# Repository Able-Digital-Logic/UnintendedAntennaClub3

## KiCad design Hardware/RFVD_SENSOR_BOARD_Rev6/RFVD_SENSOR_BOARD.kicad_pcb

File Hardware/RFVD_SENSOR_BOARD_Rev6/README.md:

# RFVD SENSOR-D board: layout handoff (2026-10-02)

This folder holds a complete KiCad 10 project of the RFVD sensor board. Placement is final and locked, and 92.6% of the board is routed (42 links left, each with a mapped path). You can open it and keep routing.

**To finish the routing, start with [`docs/ROUTING_FINISH_GUIDE.md`](docs/ROUTING_FINISH_GUIDE.md).**

**2026-10-07: ECO-002 and ECO-003 landed.** Records: `03_hardware/ECO-002_POWER_MODES.md` and `03_hardware/ECO-003_HIERARCHY_AND_LABELING.md` in the main repo.
- **ECO-002, two battery modes:**
  - SCREEN: a TPS62913 buck locked to 3 × fs;
  - RECORD: a TPS7A4701 LDO with the buck off;
  - an NFM18 RF filter (FL1301) on +3V3_A.
- **ECO-003, schematic reorganised:**
  - hierarchical sheets with a block-diagram root page, sheet index, bus-alias table and legend;
  - rail power symbols;
  - every sheet's bus ports grouped in a "SHEET INTERFACE" block;
  - designators renumbered by page (page × 100 + index, e.g. R1301), with old-to-new in [`docs/REFERENCE_MAP_ECO-003.md`](docs/REFERENCE_MAP_ECO-003.md);
  - Values carry ratings.
- **Rules:** DRU v13 and the net classes follow the renamed nets.
- **PCB:** the new parts are placed with the EMC rules, and the stale copper of the old buck and +3V3_A node is removed. DRC shows 0 shorts. Routing to do for the ECO area: [`docs/LAYOUT_STATUS.md`](docs/LAYOUT_STATUS.md), top section.
- **Placement pass (late 2026-10-07):** the TPS62913 buck (U1301) is re-laid to TI's recommended layout (SLVSFP4B Fig. 10-1): 0.7 mm switch node, input caps on the VIN/PGND pins, output-cap ground beside PGND. The LDO output cap C1311, FL1301, R1211 and TP1104 moved closer to their partners. No new copper DRC errors; the ratsnest is 27 mm shorter. Pin positions and escape vias for the hand router: `docs/LAYOUT_STATUS.md`, top section.

**Checkpoint 5 (2026-10-04), board sha256 `f9fb559366`: final state of this pass, ready for hand routing.**
- **DRC: 0 errors**, 110 warnings, sign-off PASS.
- **42 open links, 0 blocked.** `docs/ROUTING_FINISH_GUIDE.md` §0 lists each link with a suggested path and its hand-off via.
- Placement is final and every footprint is locked.
- Ratsnest 3522 mm (m17: 4018). BOM: 100 lines / 309 parts.
- Since checkpoint 4a:
  - J10 moved 0.96 mm to match the HRO drawing;
  - F1 on its Bourns Style 2 land at J2, with PACK+ as a 1 mm B-only run;
  - the U403 buffer moved out from under J10;
  - the BOM consolidation (firmware rules in FIRMWARE_CONTRACT §11);
  - the remaining DRC fixes;
  - pad escapes for every blocked link.

**Checkpoint 4a (2026-10-04), board sha256 `08570ddf0b`.**
- Five region hand-layout packages: A RF/AFE, B1/B2 MCU core, C power band, E south J11/J2. The sourcing package moved 47 parts to in-stock JLC Basic or FOJAN types and C31 to 25 V.
- **DRC 278 → 109 errors**, 116 warnings, 43 open links (was 44), missing return vias 45 → 13, neck chains 46 → 12. Sign-off PASS. ERC 0.
- What was added:
  - an AFE GND ring: a 1.0 mm band under a mask-open strip, 19 fence vias, FL1 on the east wall;
  - the 32 kHz crystal-gap via moved out of the gap;
  - the EXP_SYNC fix at J11;
  - the VSYS island at U402 routed;
  - battery trunks at 0.8 mm on In3;
  - BQ25798 hot-loop GND vias;
  - 31 edge-stitching vias.
- Next: the routing waves for the remaining errors and links (west/J10, MCU-core seam, battery, then the LCD and expansion buses).

**Checkpoint 3 (2026-10-04), board sha256 `527e801c62`.**
- The stricter rules v11 landed: side-aware exemptions, neck caps, In3 power widths, missing keep-outs, pre-defined sizes, mask 0.
- Every stale sheet note and Function field was corrected.
- DRC now shows **278 errors**, on purpose. They are the copper the old rules hid (power widths and necks, 3W spacing, foreign copper under J10), and they are checkpoint 4's routing work list (`docs/LAYOUT_STATUS.md`, Checkpoint 3).
- ERC 0, 44 open links, sign-off rules PASS.

**Checkpoint 2b (2026-10-04), board sha256 `f539f0317c`. DRC: 0 errors.**
- **SD:** an ST EMIF06 SD front end replaces 20 parts and clears both SD skew errors.
- **PSRAM:** one series array.
- **Display bus:** resistors regrouped by pin side.
- **MCU/service:** SWO, the BOOT button and the lid interrupt are removed; the buttons get series resistors.
- **Expansion:** pull-ups added, ESD flow-through, the MR-kill jumpers are gone.
- **Back silkscreen:** an issue date and a serial-number box. A fab note sits on User.Drawings.
- **J10:** pin-in-paste on its shell.

Totals: 538/582 routed (44 open), 82 warnings (each explained in `docs/LAYOUT_STATUS.md`), sign-off PASS. JLC BOM: 106 lines / 318 parts. The manufacturing spec and the panel tool are in `docs/MANUFACTURING_EMC_SPEC.md` and `tools/make_panel.py`; the panel is a 72 × 90 mm 1-up frame, so exactly 2 boards are assembled.

**Checkpoint 2a (2026-10-04), board sha256 `c4383fe7ab`.** The circuit changes from the critique landed:
- the AD7380 runs on its internal reference;
- the EREF filter is a single pole;
- 33R / 2.2 nF ADC reservoirs;
- buck FB divider 23.2k/10k;
- eFuse OVLO 64.9k;
- display straps in copper and a write-only bus;
- the VSYS and VBUS dividers, the charge LED and two polymer caps are gone;
- the 1 µF line merged.

30 parts removed, 2 added. DRC: 2 errors (both `skew_sdmmc`, until SD_D1 is routed), 85 warnings; sign-off PASS. ERC is clean. 47 open links (was 50). The JLC BOM is 105 lines / 346 parts (was 111 / 369). An independent review checked every change against its datasheet. Details: `docs/LAYOUT_STATUS.md` (Checkpoint 2a); firmware consequences: `docs/FIRMWARE_NOTES.md`.

**Checkpoint 1 (2026-10-04), board sha256 `5c22d06d54`.** The first batch from the full design critique and the placement revision landed:
- placement and EMC fixes in the RF, analog, expansion, charger/USB, buck and battery areas;
- a 22.9 mm antenna stub deleted;
- overlapping drills fixed;
- silkscreen labels and the board ID moved onto the board;
- schematic DNP flags fixed, so the BOM now includes the FB1 damper.

DRC warnings went from 97 to 87 (counted in this folder), ERC is clean, and no connection got worse. Details: `docs/LAYOUT_STATUS.md` (Checkpoint 1); the plan for the rest: `docs/WORKPLAN_2026-10-03.md`.

**Update 2026-10-03 (hand-layout pass, no auto-routers):**
- Every edit was an explicit coordinate list (`docs/hand_edits_2026-10-03/`).
- **DRC errors 14 → 3; warnings 212 → 153.** The VSYS trunk is closed.
- R304, R411, R404 and R417 were re-placed. The BUCK_SYNC spacing now passes the 3W and the 3 mm LSE sign-off rules.
- The rest of the board is handed over for interactive push-and-shove routing, with a measured, step-by-step guide.
- J3 has no legal alternative pose (checked), so the band is solved by re-fanning escapes, not by moving the big parts.

**Update 2026-10-02 night:**
- The board was **widened to 52.05 x 90.05 mm**: +2.5 mm per side, with a notch that keeps the USB-C and microSD flush.
- A connection-length **placement audit** was added: `docs/PLACEMENT_AUDIT.md` and `outputs/RFVD_placement_audit_*`.
- R314 and Q302 moved next to their partners, and 5 more connections plus all GND islands were routed.
- A DRC clean-up took the errors from 50 to 14:
  - shield pads now connect solidly to the GND pours;
  - an SWDIO via too close to a J10 hole was re-routed, and the router now models that rule;
  - 3 clearance problems were re-routed locally;
  - two scoped rule exceptions were added (DRU patch v10).
- The tools were cleaned into one self-tested folder: `tools/README.md`.
- The board before this pass is in `backups/RFVD_SENSOR_BOARD_before_widening_2026-10-02.kicad_pcb`.

The project folder `03_hardware/RFVD_SENSOR_BOARD_GITHUB` was **not** modified. Everything here was built from it on scratch copies; the base board hash was `2ccd301640`.

Open **`RFVD_SENSOR_BOARD.kicad_pro`** in KiCad 10. The libraries and 3D models are included and use project-relative paths.

## Status at a glance (checkpoint 5, board sha256 `f9fb559366`)

| Item | State |
|---|---|
| Outline | **52.05 x 90.05 mm** (widened 2026-10-02 from 47.05 mm; port notch at y 104.6-133.3 keeps J3/J10 flush). Fits the 56 mm box: west gap 2.75 mm (5.25 at the ports), east 1.25 mm. |
| Placement | **Final and locked**: 341 footprints (196 top / 145 bottom), all locked. Placed against each IC's datasheet layout guide (`docs/sensitivity.json`, with section and page). The 2026-10-04 sign-off on the board: **placeaudit 0 MOVE / 0 OVER**; `tools/dsgap.py` measured 269 datasheet budgets, 264 within budget and 5 justified with measured reasons (`docs/PLACEMENT_DATASHEET_CHECK.md`, `tools/placeaudit_keep.json`). |
| Routing | **524 of 566 connections (92.6%)**; the total was 633 before the BOM consolidation removed parts. **42 open links, 0 blocked**: 12 direct, 30 with a mapped legal path. Every link is in `docs/ROUTING_FINISH_GUIDE.md` §0 with exact coordinates. No GND islands. |
| Copper | 3,038 mm of track (F 994 / In3 1,047 / B 997 mm), 1,028 vias (941 of them 0.45/0.20 POFV), 7 copper zones, 45 rule areas. |
| DRC (`outputs/RFVD_DRC_report.*`) | **0 errors**, 110 warnings (each class explained in `docs/LAYOUT_STATUS.md`, Checkpoint 5; 42 of them are the deliberate hand-off vias), sign-off PASS. Always run DRC with `--all-track-errors` from the CLI. |
| Silkscreen | No reference designator is visible on F/B silkscreen; they stay on the fab layers. |
| BOM | Regenerated by `tools/make_outputs.py` from KiCad's own DNP flags: **100 lines / 309 placed parts**, every one with MPN and LCSC number. The CPL has exactly those designators, rotation-corrected for JLC. Live stock check 2026-10-04 (`docs/LAYOUT_STATUS.md`): 95 lines are in JLC stock for 2 boards and 4 come from LCSC via a parts pre-order. **L1 (XGL4020-472MEC) needs the Global Sourcing route: JLC holds 1.** |
| Fab outputs | **Not generated on purpose** until the last 42 links are routed. Then run `tools/make_fab_outputs.py` and `tools/make_panel.py` (D27: 1-up 72 x 90 mm frame). |

## What is left to route (`outputs/RFVD_unrouted.csv`, `outputs/RFVD_unrouted.png`)

| Group | Open | Nets |
|---|---|---|
| Expansion to J11 | 15 | EXP_3V3_SNS, EXP_ANA_MON, EXP_CS0_N_MCU, EXP_CS1_N_MCU, EXP_DETECT_N_MCU, EXP_GATE, EXP_INT1_N_MCU, EXP_IO0_MCU, EXP_IO1_MCU, EXP_MISO_MCU, EXP_RST_N_MCU, EXP_SPI_MOSI, EXP_SPI_SCK, EXP_SYNC, EXP_VHP_SNS |
| LCD bus to J4 | 14 | LCD_BL, LCD_BL_SW, LCD_CS_N, LCD_D0-LCD_D7, LCD_DC, LCD_LED_K4, LCD_WR_N |
| Power / charger | 6 | CHG_INT_N, QON_N, USB_DM, USB_DP (2 islands), VBAT_RTC |
| Other | 7 | MARK_N, NRST, PSRAM_IO2_RAM, RECORD_N, SD_D1_MCU, TP_INT, TP_SCL |
| GND | 0 | All GND islands are joined. |

Each link, with both ends, the suggested path and its hand-off via, is in **`docs/ROUTING_FINISH_GUIDE.md` §0**. The history and root causes are in `docs/LAYOUT_STATUS.md`.

## What to do next

1. **Do the GUI-only setup steps** in `docs/LEAD_GUI_STEPS.md` (stackup loss, via filling, silk minimums, J10 shell paste). The two optional placement clean-ups (A, B) are listed there too.
2. **Route the 42 open links** with KiCad's interactive router in push-and-shove mode, following `docs/ROUTING_FINISH_GUIDE.md` §0:
   - set the pre-defined sizes first (0.45/0.20 vias, 0.15 mm tracks);
   - start each link from its hand-off via;
   - octilinear tracks, fillets on clocks and strobes.
   Footprints are locked, so push-and-shove moves only tracks.
3. **Add a GND return via** at every layer change of a fast net (R17: within 1.0 mm for clocks, 1.5 mm for digital).
4. **Re-run DRC** with the project rule file (`RFVD_SENSOR_BOARD.kicad_dru`) and `--all-track-errors`; the goal is 0 errors and no new warning class.
5. **Regenerate the outputs**: `tools/make_outputs.py` (run it in this folder), then the fab outputs and the panel (`tools/make_fab_outputs.py`, `tools/make_panel.py --cols 1 --min-size 72`). Check the CPL rotations in JLCPCB's preview before ordering.
6. **Copy the result back** into `RFVD_SENSOR_BOARD_GITHUB`: replace the board, rule file and project file there, or follow the Konnect transfer plan in `docs/CHANGES_FROM_PROJECT.md`.

## Folder map

| Path | Contents |
|---|---|
| `RFVD_SENSOR_BOARD.kicad_pro/.kicad_pcb/.kicad_dru` | Project, routed board (this handoff) and design rules. |
| `*.kicad_sch` | Schematic: root plus 11 sheets, unchanged from the project. |
| `libraries/`, `models/`, `fp-lib-table`, `sym-lib-table` | Custom symbols, footprints and 3D models (project-relative). |
| `outputs/` | BOMs, JLCPCB BOM/CPL, position file, schematic PDF, multi-page layer PDF, DRC report, unrouted list and map. See `outputs/README.md`. |
| `renders/` | 3D renders (top/bottom) and one image per copper layer with footprint outlines (`layer_1_F_Cu.png` ... `layer_6_B_Cu.png`). |
| `docs/` | Board overview, layout status, changes from the project, tools guide, placement sensitivity study, and the original reports (`docs/reference/`). |
| `tools/` | The single, self-tested layout toolset: router, placement audit, placement, widening, merge, DRC and output helpers. Index: `tools/README.md`; check it with `tools/selftest.py`; regenerate every output with `tools/make_outputs.py`. |

## Documents

- `docs/BOARD_OVERVIEW.md`: what the board does, blocks and key parts, stack-up, net classes, EMC strategy, placement philosophy.
- `docs/ROUTING_FINISH_GUIDE.md`: **how to finish the last 50 links interactively**. It covers every link with today's feasibility, the verified unlock moves, the J4 via sites, the rule areas the router does not enforce, router set-up and order of work. Maps are in `docs/routing_guide/`.
- `docs/LAYOUT_STATUS.md`: routing status per group, root causes, recommended fixes, the DRC error list, and decisions and deviations.
- `docs/CHANGES_FROM_PROJECT.md`: everything that differs from `RFVD_SENSOR_BOARD_GITHUB`, and how to bring it back.
- `docs/PLACEMENT_DATASHEET_CHECK.md`: every part against its IC's datasheet layout rule, measured on the board (generated by `tools/dsgap.py`), with the reason for each part kept over its budget.
- `docs/LEAD_GUI_STEPS.md`: the steps only the KiCad GUI can do, and the optional placement clean-ups.
- `docs/PLACEMENT_AUDIT.md`: the placement audit (what was flagged, moved and kept, with reasons) and the board widening.
- `tools/README.md`: the layout tools and how to re-run them (`docs/TOOLS.md` points there).
- `docs/sensitivity_summary.md` / `docs/sensitivity.json`: per-part datasheet placement budgets.
- `docs/reference/`: the project's device report, PCB layout rationale and EMC report (.docx), plus sheet images.

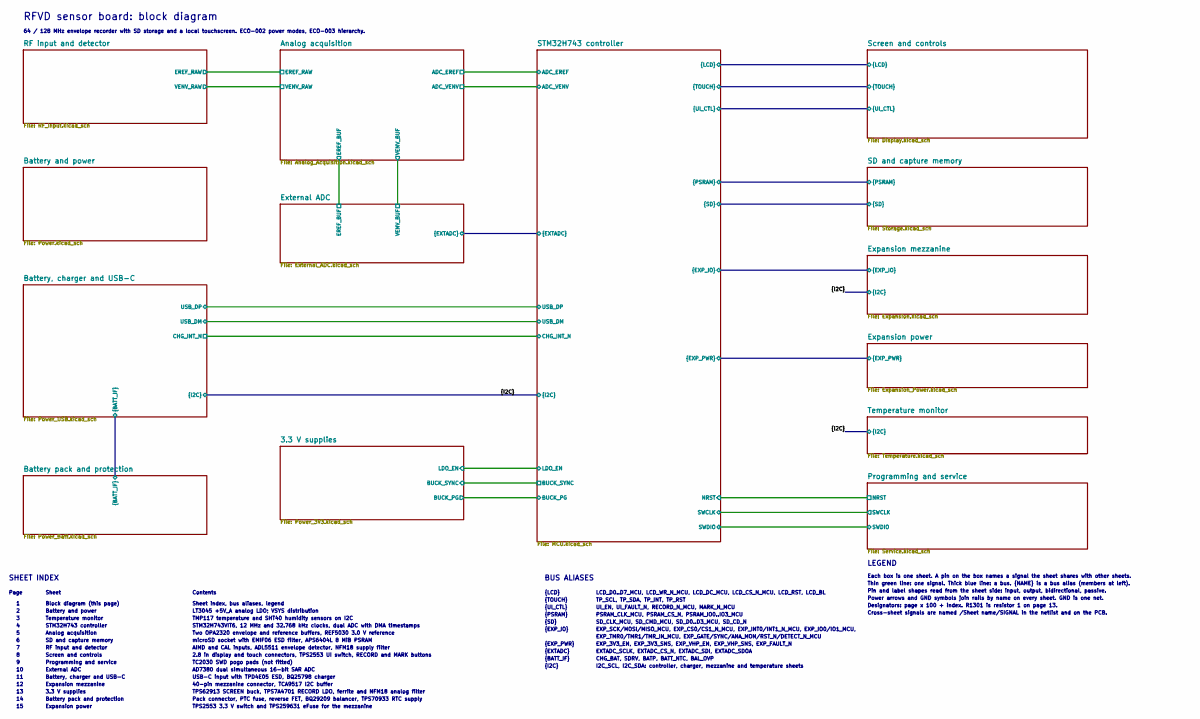
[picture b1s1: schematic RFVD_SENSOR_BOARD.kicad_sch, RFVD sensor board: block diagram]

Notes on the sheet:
TMP117 temperature and SHT40 humidity sensors on I2C
Thin green line: one signal. Thick blue line: a bus. {NAME} is a bus alias (members at left).
Designators: page x 100 + index. R1301 is resistor 1 on page 13.
Sheet index, bus aliases, legend
STM32H743 controller
Programming and service
Pin and label shapes read from the sheet side: input, output, bidirectional, passive.
Power arrows and GND symbols join rails by name on every sheet. GND is one net.
{I2C}
Each box is one sheet. A pin on the box names a signal the sheet shares with other sheets.
Sheet
USB-C input with TPD4E05 ESD, BQ25798 charger
Analog acquisition
LEGEND
TPS62913 SCREEN buck, TPS7A4701 RECORD LDO, ferrite and NFM18 analog filter
SD_CLK_MCU, SD_CMD_MCU, SD_D0..D3_MCU, SD_CD_N
EXP_TMR0/TMR1/TMR_IN_MCU, EXP_GATE/SYNC/ANA_MON/RST_N/DETECT_N_MCU
Pack connector, PTC fuse, reverse FET, BQ29209 balancer, TPS70933 RTC supply
LT3045 +5V_A analog LDO; VSYS distribution
{BATT_IF}
PSRAM_CLK_MCU, PSRAM_CS_N, PSRAM_IO0..IO3_MCU
EXP_SCK/MOSI/MISO_MCU, EXP_CS0/CS1_N_MCU, EXP_INT0/INT1_N_MCU, EXP_IO0/IO1_MCU,
I2C_SCL, I2C_SDA: controller, charger, mezzanine and temperature sheets
Battery and power
Cross-sheet signals are named /Sheet name/SIGNAL in the netlist and on the PCB.
STM32H743VIT6, 12 MHz and 32.768 kHz clocks, dual ADC with DMA timestamps
{EXP_PWR}
Page
{EXP_IO}
Temperature monitor
Battery, charger and USB-C
Contents
AD7380 dual simultaneous 16-bit SAR ADC
{UI_CTL}
CHG_BAT, SDRV, BATP, BATT_NTC, BAL_OVP
UI_EN, UI_FAULT_N, RECORD_N_MCU, MARK_N_MCU
BUS ALIASES
{PSRAM}
RF input and detector
Two OPA2320 envelope and reference buffers, REF5030 3.0 V reference

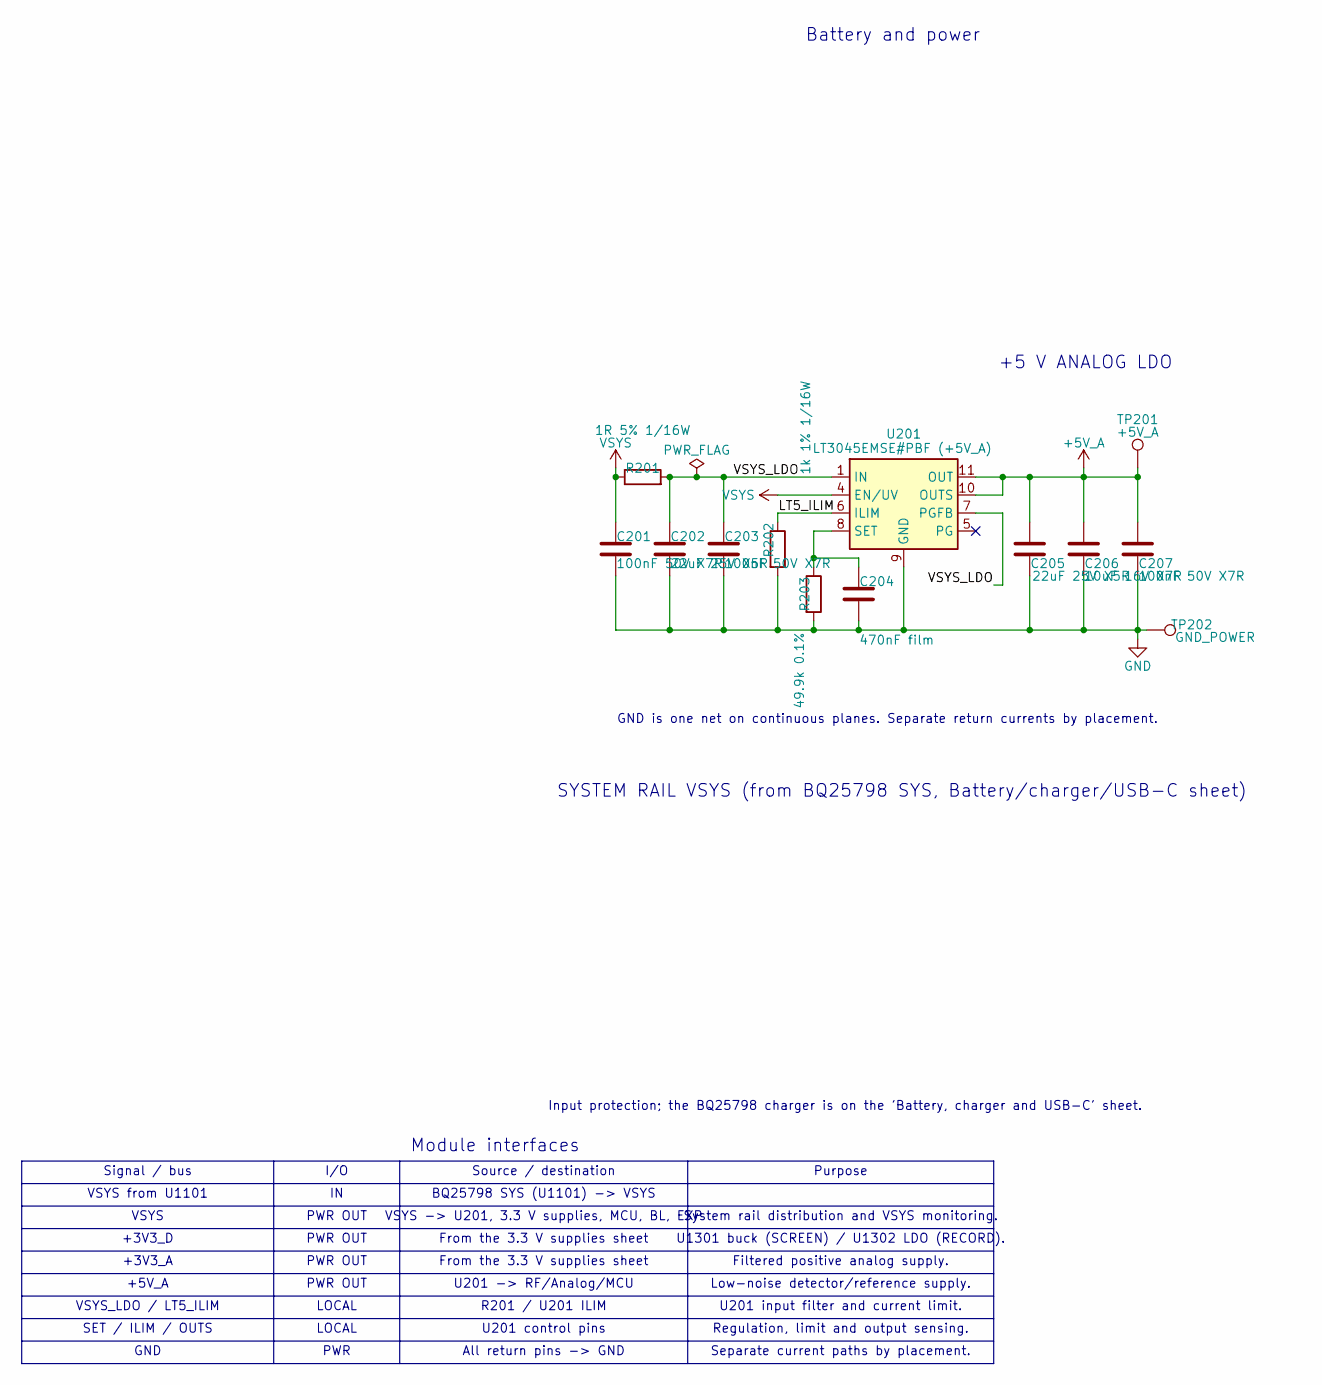
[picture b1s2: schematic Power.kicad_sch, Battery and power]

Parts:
C201: 100nF 50V X7R; C_0603_1608Metric; MPN CC0603KRX7R9BB104; LCSC C14663
C202, C205: 22uF 25V X5R; C_1206_3216Metric; MPN CL31A226KAHNNNE; LCSC C12891
C203, C207: 100nF 50V X7R; C_0402_1005Metric; MPN CL05B104KB54PNC; LCSC C307331
C204: 470nF film; C_1206_3216Metric; MPN 35MU474KA13216; LCSC C3773390
C206: 10uF 16V X7R; C_0805_2012Metric; MPN CL21B106KOQNNNE; LCSC C95841
R201: 1R 5% 1/16W; R_0402_1005Metric; MPN FRC0402J1R0 TS; JLCPCB_PN C2906901
R202: 1k 1% 1/16W; R_0402_1005Metric; MPN 0402WGF1001TCE; LCSC C11702
R203: 49.9k 0.1%; R_0603_1608Metric; MPN ERA3AEB4992V; LCSC C491136
TP201: +5V_A; TestPoint_Pad_D1.0mm; MPN DNP-NO-COMPONENT; LCSC N/A
TP202: GND_POWER; TestPoint_Pad_D1.0mm; MPN PCB_PAD
U201: LT3045EMSE#PBF (+5V_A); MSOP-12-1EP_3x4.039mm_P0.65mm_EP1.651x2.845mm; MPN LT3045EMSE#PBF; JLCPCB_PN C580012

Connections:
+5V_A: C205.1, C206.1, C207.1, TP201.1 (1_1), U201.10 (OUTS), U201.11 (OUT), U201.12 (OUT); also elsewhere on the board
/Battery and power/LT5_ILIM: R202.1, U201.6 (ILIM)
/Battery and power/VSYS_LDO: C202.1, C203.1, R201.2, U201.1 (IN), U201.2 (IN), U201.3 (IN), U201.7 (PGFB)
GND: C201.2, C202.2, C203.2, C204.2, C205.2, C206.2, C207.2, R202.2, R203.2, TP202.1 (1_1), U201.9 (GND), U201.13 (GND); also elsewhere on the board
unnamed: C204.1, R203.1, U201.8 (SET)
VSYS: C201.1, R201.1, U201.4 (EN/UV); also elsewhere on the board

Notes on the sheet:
+3V3_A
VSYS
+3V3_D
GND
I/O
VSYS -> U201, 3.3 V supplies, MCU, BL, EXP
From the 3.3 V supplies sheet
Battery and power
LOCAL
SYSTEM RAIL VSYS (from BQ25798 SYS, Battery/charger/USB-C sheet)
SET / ILIM / OUTS
VSYS_LDO / LT5_ILIM
BQ25798 SYS (U1101) -> VSYS
Input protection; the BQ25798 charger is on the 'Battery, charger and USB-C' sheet.
U201 -> RF/Analog/MCU
Signal / bus
Module interfaces
All return pins -> GND
U1301 buck (SCREEN) / U1302 LDO (RECORD).
R201 / U201 ILIM
VSYS from U1101
+5V_A
U201 input filter and current limit.
Separate current paths by placement.
PWR OUT
+5 V ANALOG LDO
GND is one net on continuous planes. Separate return currents by placement.
Source / destination
Low-noise detector/reference supply.
U201 control pins
Regulation, limit and output sensing.
Filtered positive analog supply.
System rail distribution and VSYS monitoring.
PWR
Purpose

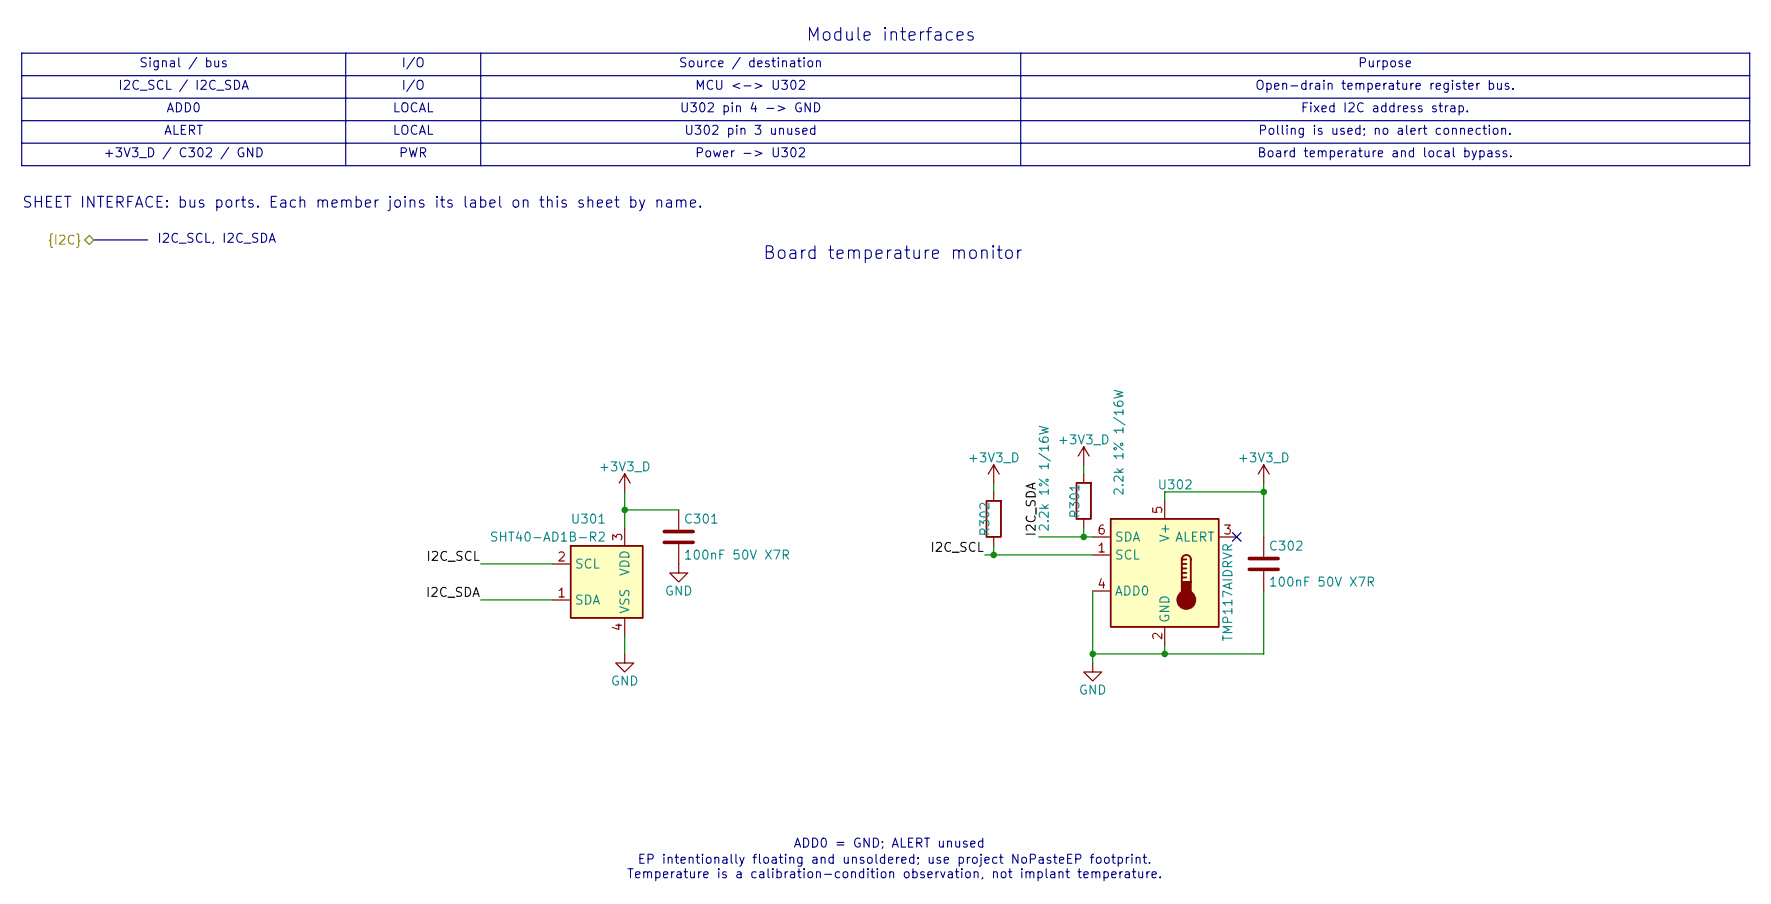
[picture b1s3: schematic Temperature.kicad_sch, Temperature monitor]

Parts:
C301: 100nF 50V X7R; C_0402_1005Metric; MPN CL05B104KB54PNC; JLCPCB_PN C307331
C302: 100nF 50V X7R; C_0402_1005Metric; MPN CL05B104KB54PNC; LCSC C307331
R301, R302: 2.2k 1% 1/16W; R_0402_1005Metric; MPN 0402WGF2201TCE; LCSC C25879
U301: SHT40-AD1B-R2; Sensirion_DFN-4_1.5x1.5mm_P0.8mm_SHT4x_NoCentralPad; MPN SHT40-AD1B-R702; JLCPCB_PN C2909890
U302: TMP117AIDRVR; TMP117_DRV_WSON6_NoPasteEP; MPN TMP117AIDRVR; JLCPCB_PN C699536

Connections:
+3V3_D: C301.1, C302.1, R301.2, R302.2, U301.3 (VDD), U302.5 (V+); also elsewhere on the board
/I2C_SCL: R302.1, U301.2 (SCL), U302.1 (SCL); also elsewhere on the board
/I2C_SDA: R301.1, U301.1 (SDA), U302.6 (SDA); also elsewhere on the board
GND: C301.2, C302.2, U301.4 (VSS), U302.2 (GND), U302.4 (ADD0); also elsewhere on the board

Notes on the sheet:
I2C_SCL / I2C_SDA
Fixed I2C address strap.
Board temperature and local bypass.
+3V3_D / C302 / GND
LOCAL
U302 pin 3 unused
Board temperature monitor
ADD0 = GND; ALERT unused
Source / destination
ALERT
PWR
Open-drain temperature register bus.
ADD0
U302 pin 4 -> GND
I2C_SCL, I2C_SDA
EP intentionally floating and unsoldered; use project NoPasteEP footprint. Temperature is a calibration-condition observation, not implant temperature.
Module interfaces
Purpose
Signal / bus
Polling is used; no alert connection.
Power -> U302
I/O
SHEET INTERFACE: bus ports. Each member joins its label on this sheet by name.
MCU <-> U302

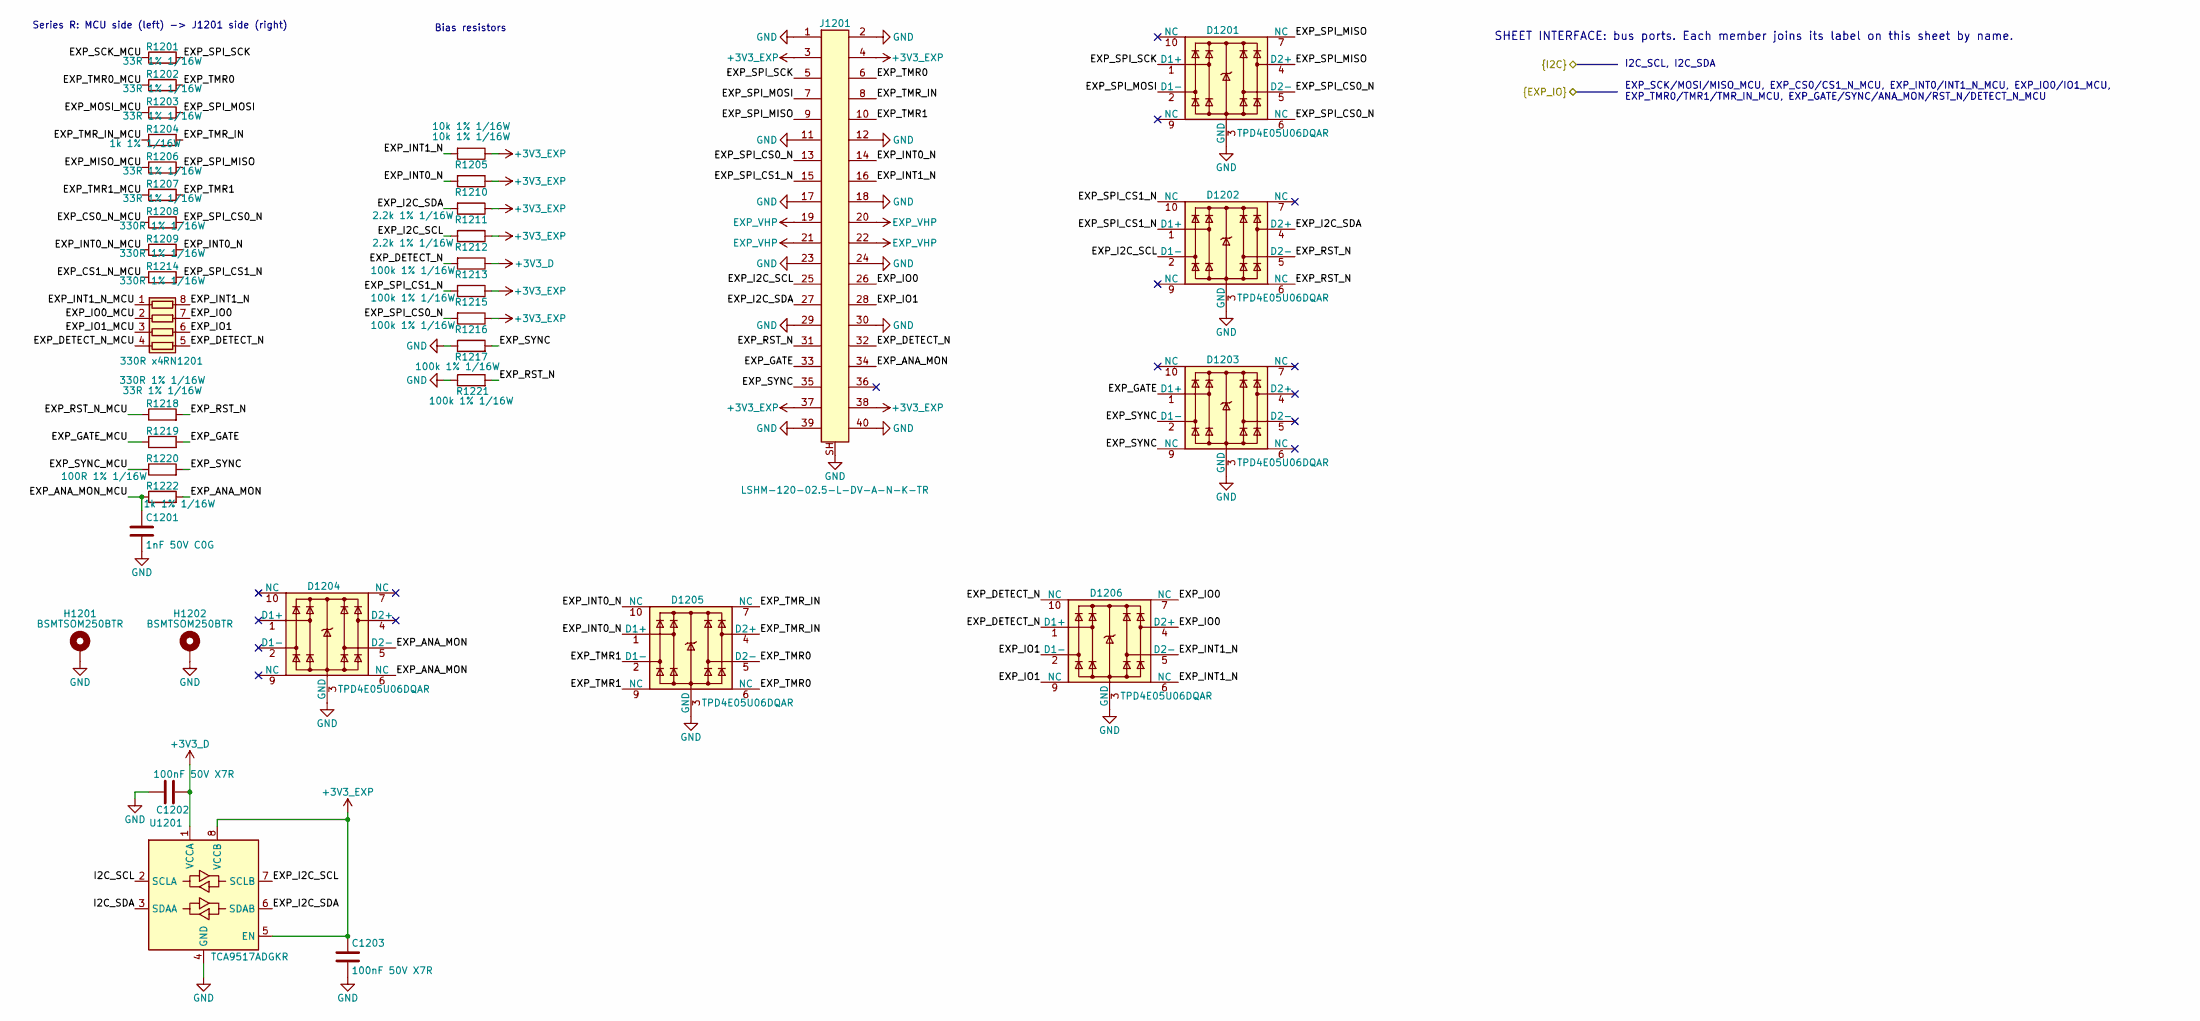
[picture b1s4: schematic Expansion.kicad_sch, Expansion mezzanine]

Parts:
C1201: 1nF 50V C0G; C_0402_1005Metric; MPN GRM1555C1H102JA01D; JLCPCB_PN C76947
C1202, C1203: 100nF 50V X7R; C_0402_1005Metric; MPN CL05B104KB54PNC; JLCPCB_PN C307331
D1201, D1202, D1203, D1204, D1205, D1206: TPD4E05U06DQAR; USON-10_2.5x1.0mm_P0.5mm; MPN TPD4E05U06DQAR; JLCPCB_PN C138714
H1201, H1202: BSMTSOM250BTR; Standoff_SMT_M2_BZXC_BSMTSOM2_Hole3.8mm_Pad6.2mm; MPN BSMTSOM250BTR; JLCPCB_PN C20617226
J1201: LSHM-120-02.5-L-DV-A-N-K-TR; Samtec_LSHM-120-xx.x-x-DV-S_2x20-1SH_P0.50mm_Vertical; MPN LSHM-120-02.5-L-DV-A-N-K-TR; JLCPCB_PN C6287797
R1201, R1202, R1203, R1206, R1207, R1219: 33R 1% 1/16W; R_0402_1005Metric; MPN 0402WGF330JTCE; JLCPCB_PN C25105
R1204, R1222: 1k 1% 1/16W; R_0402_1005Metric; MPN 0402WGF1001TCE; JLCPCB_PN C11702
R1205, R1210: 10k 1% 1/16W; R_0402_1005Metric; MPN 0402WGF1002TCE; JLCPCB_PN C25744
R1208, R1209, R1214, R1218: 330R 1% 1/16W; R_0402_1005Metric; MPN 0402WGF3300TCE; JLCPCB_PN C25104
R1211, R1212: 2.2k 1% 1/16W; R_0402_1005Metric; MPN 0402WGF2201TCE; JLCPCB_PN C25879
R1213, R1215, R1216, R1217, R1221: 100k 1% 1/16W; R_0402_1005Metric; MPN 0402WGF1003TCE; JLCPCB_PN C25741
R1220: 100R 1% 1/16W; R_0402_1005Metric; MPN 0402WGF1000TCE; JLCPCB_PN C25076
RN1201: 330R x4; R_Array_Convex_4x0402; MPN 4D02WGJ0331TCE; JLCPCB_PN C43557
U1201: TCA9517ADGKR; VSSOP-8_3x3mm_P0.65mm; MPN TCA9517ADGKR; JLCPCB_PN C201698

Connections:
+3V3_D: C1202.1, R1213.1, U1201.1 (VCCA); also elsewhere on the board
+3V3_EXP: C1203.1, J1201.3, J1201.4, J1201.37, J1201.38, R1205.1, R1210.1, R1211.1, R1212.1, R1215.1, R1216.1, U1201.5 (EN), U1201.8 (VCCB); also elsewhere on the board
/Expansion mezzanine/EXP_ANA_MON: D1204.5 (D2-), D1204.6 (NC), J1201.34, R1222.2
/Expansion mezzanine/EXP_ANA_MON_MCU: C1201.1, R1222.1; also elsewhere on the board
/Expansion mezzanine/EXP_CS0_N_MCU: R1208.1; also elsewhere on the board
/Expansion mezzanine/EXP_CS1_N_MCU: R1214.1; also elsewhere on the board
/Expansion mezzanine/EXP_DETECT_N: D1206.1 (D1+), D1206.10 (NC), J1201.32, R1213.2, RN1201.5 (R4.2)
/Expansion mezzanine/EXP_DETECT_N_MCU: RN1201.4 (R4.1); also elsewhere on the board
/Expansion mezzanine/EXP_GATE: D1203.1 (D1+), J1201.33, R1219.2
/Expansion mezzanine/EXP_GATE_MCU: R1219.1; also elsewhere on the board
/Expansion mezzanine/EXP_I2C_SCL: D1202.2 (D1-), J1201.25, R1212.2, U1201.7 (SCLB)
/Expansion mezzanine/EXP_I2C_SDA: D1202.4 (D2+), J1201.27, R1211.2, U1201.6 (SDAB)
/Expansion mezzanine/EXP_INT0_N: D1205.1 (D1+), D1205.10 (NC), J1201.14, R1209.2, R1210.2
/Expansion mezzanine/EXP_INT0_N_MCU: R1209.1; also elsewhere on the board
/Expansion mezzanine/EXP_INT1_N: D1206.5 (D2-), D1206.6 (NC), J1201.16, R1205.2, RN1201.8 (R1.2)
/Expansion mezzanine/EXP_INT1_N_MCU: RN1201.1 (R1.1); also elsewhere on the board
/Expansion mezzanine/EXP_IO0: D1206.4 (D2+), D1206.7 (NC), J1201.26, RN1201.7 (R2.2)
/Expansion mezzanine/EXP_IO0_MCU: RN1201.2 (R2.1); also elsewhere on the board
/Expansion mezzanine/EXP_IO1: D1206.2 (D1-), D1206.9 (NC), J1201.28, RN1201.6 (R3.2)
/Expansion mezzanine/EXP_IO1_MCU: RN1201.3 (R3.1); also elsewhere on the board
/Expansion mezzanine/EXP_MISO_MCU: R1206.1; also elsewhere on the board
/Expansion mezzanine/EXP_MOSI_MCU: R1203.1; also elsewhere on the board
/Expansion mezzanine/EXP_RST_N: D1202.5 (D2-), D1202.6 (NC), J1201.31, R1218.2, R1221.2
/Expansion mezzanine/EXP_RST_N_MCU: R1218.1; also elsewhere on the board
/Expansion mezzanine/EXP_SCK_MCU: R1201.1; also elsewhere on the board
/Expansion mezzanine/EXP_SPI_CS0_N: D1201.5 (D2-), D1201.6 (NC), J1201.13, R1208.2, R1216.2
/Expansion mezzanine/EXP_SPI_CS1_N: D1202.1 (D1+), D1202.10 (NC), J1201.15, R1214.2, R1215.2
/Expansion mezzanine/EXP_SPI_MISO: D1201.4 (D2+), D1201.7 (NC), J1201.9, R1206.2
/Expansion mezzanine/EXP_SPI_MOSI: D1201.2 (D1-), J1201.7, R1203.2
/Expansion mezzanine/EXP_SPI_SCK: D1201.1 (D1+), J1201.5, R1201.2
/Expansion mezzanine/EXP_SYNC: D1203.2 (D1-), D1203.9 (NC), J1201.35, R1217.2, R1220.2
/Expansion mezzanine/EXP_SYNC_MCU: R1220.1; also elsewhere on the board
/Expansion mezzanine/EXP_TMR0: D1205.5 (D2-), D1205.6 (NC), J1201.6, R1202.2
/Expansion mezzanine/EXP_TMR0_MCU: R1202.1; also elsewhere on the board
/Expansion mezzanine/EXP_TMR1: D1205.2 (D1-), D1205.9 (NC), J1201.10, R1207.2
/Expansion mezzanine/EXP_TMR1_MCU: R1207.1; also elsewhere on the board
/Expansion mezzanine/EXP_TMR_IN: D1205.4 (D2+), D1205.7 (NC), J1201.8, R1204.2
/Expansion mezzanine/EXP_TMR_IN_MCU: R1204.1; also elsewhere on the board
/I2C_SCL: U1201.2 (SCLA); also elsewhere on the board
/I2C_SDA: U1201.3 (SDAA); also elsewhere on the board
EXP_VHP: J1201.19, J1201.20, J1201.21, J1201.22; also elsewhere on the board
GND: C1201.2, C1202.2, C1203.2, D1201.3 (GND), D1201.8 (GND), D1202.3 (GND), D1202.8 (GND), D1203.3 (GND), D1203.8 (GND), D1204.3 (GND), D1204.8 (GND), D1205.3 (GND), D1205.8 (GND), D1206.3 (GND), D1206.8 (GND), H1201.1 (1_1), H1202.1 (1_1), J1201.1, J1201.2, J1201.11, J1201.12, J1201.17, J1201.18, J1201.23, J1201.24, J1201.29, J1201.30, J1201.39, J1201.40, J1201.SH (Shield), R1217.1, R1221.1, U1201.4 (GND); also elsewhere on the board

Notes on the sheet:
Bias resistors
I2C_SCL, I2C_SDA
Series R: MCU side (left) -> J1201 side (right)
EXP_SCK/MOSI/MISO_MCU, EXP_CS0/CS1_N_MCU, EXP_INT0/INT1_N_MCU, EXP_IO0/IO1_MCU, EXP_TMR0/TMR1/TMR_IN_MCU, EXP_GATE/SYNC/ANA_MON/RST_N/DETECT_N_MCU
SHEET INTERFACE: bus ports. Each member joins its label on this sheet by name.

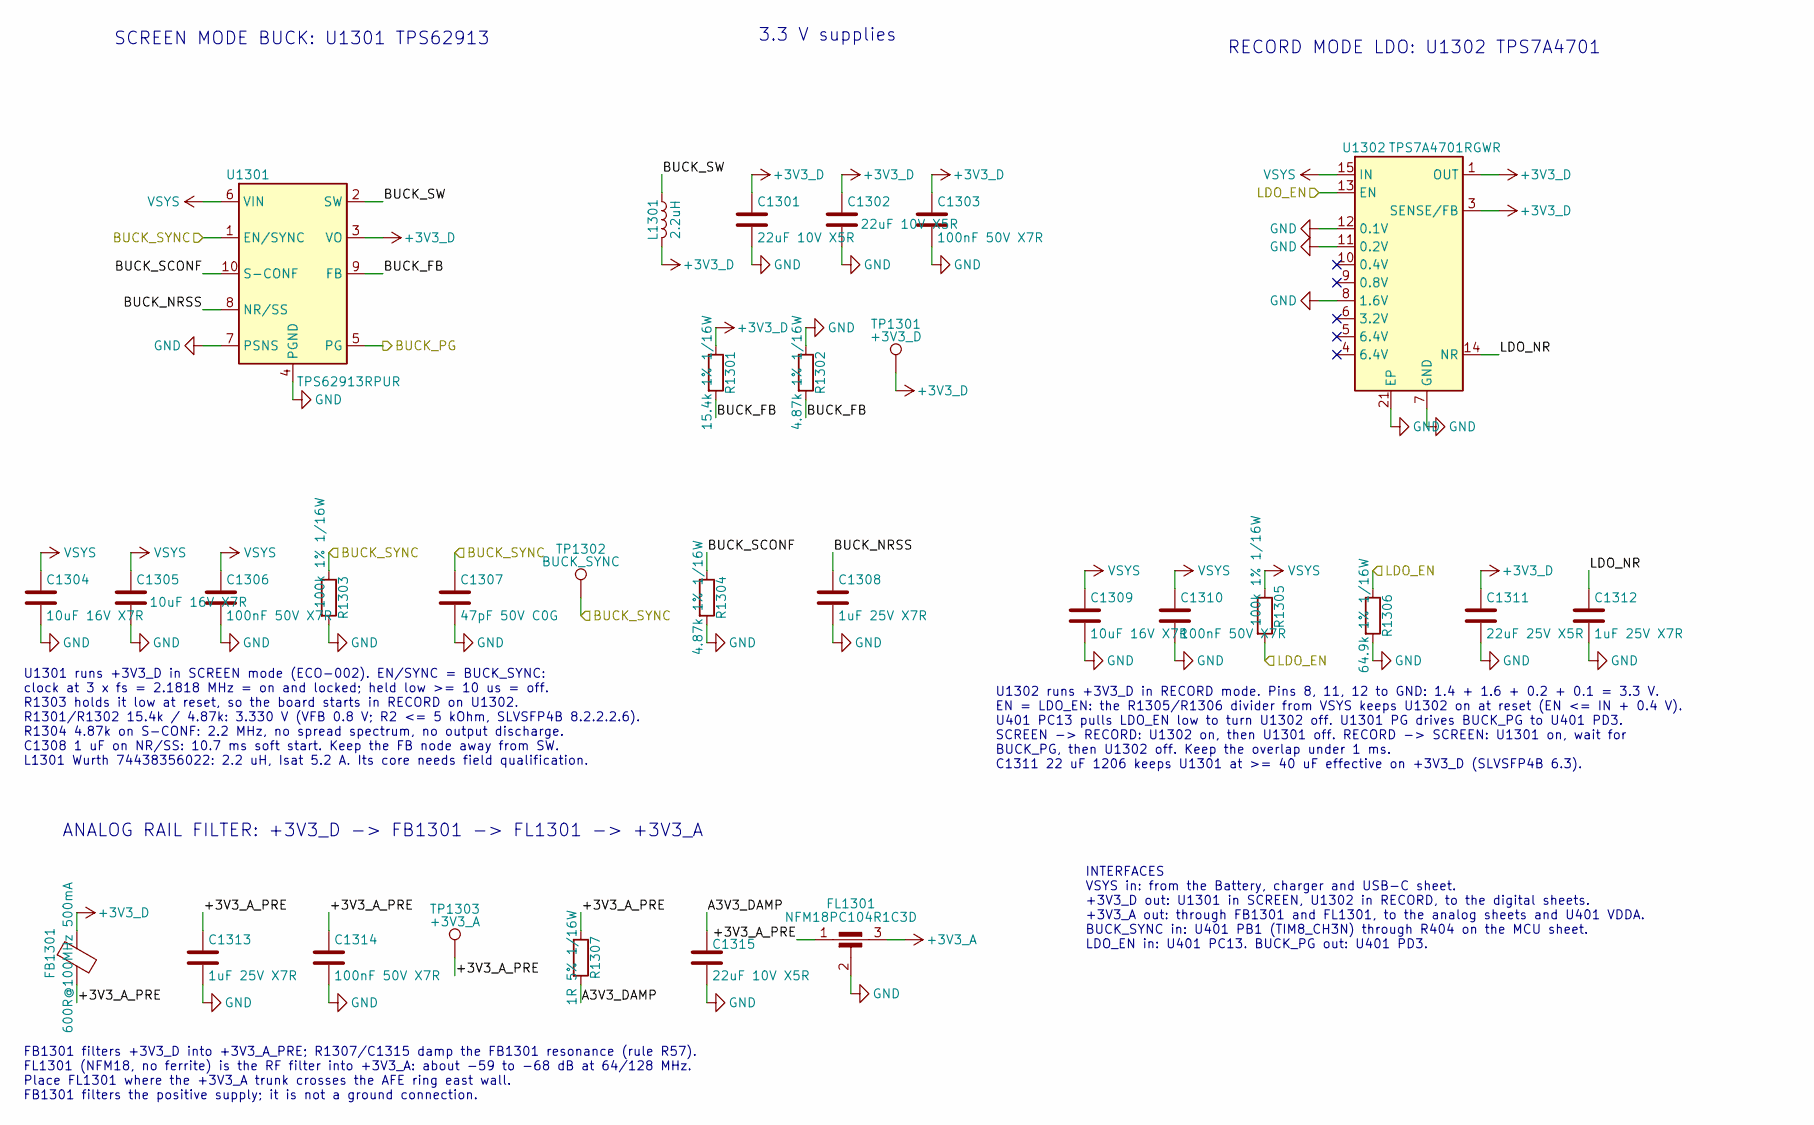
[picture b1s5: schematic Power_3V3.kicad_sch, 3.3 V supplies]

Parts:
C1301, C1302, C1315: 22uF 10V X5R; C_0805_2012Metric; MPN CL21A226MPQNNNE; JLCPCB_PN C29277
C1303, C1306, C1310, C1314: 100nF 50V X7R; C_0402_1005Metric; MPN CL05B104KB54PNC; JLCPCB_PN C307331
C1304, C1305, C1309: 10uF 16V X7R; C_0805_2012Metric; MPN CL21B106KOQNNNE; JLCPCB_PN C95841
C1307: 47pF 50V C0G; C_0402_1005Metric; MPN 0402CG470J500NT; JLCPCB_PN C1567
C1308, C1312, C1313: 1uF 25V X7R; C_0603_1608Metric; MPN CL10B105KA8NNNC; JLCPCB_PN C29936
C1311: 22uF 25V X5R; C_1206_3216Metric; MPN CL31A226KAHNNNE; JLCPCB_PN C12891
FB1301: 600R@100MHz 500mA; L_0603_1608Metric; MPN BLM18AG601SN1D; JLCPCB_PN C19330
FL1301: NFM18PC104R1C3D; Murata_NFM18PC_0603_3T; MPN NFM18PC104R1C3D; JLCPCB_PN C111493
L1301: 2.2uH; L_Wuerth_MAPI-4020; MPN 74438356022
R1301: 15.4k 1% 1/16W; R_0402_1005Metric; MPN 0402WGF1542TCE; JLCPCB_PN C62740
R1302, R1304: 4.87k 1% 1/16W; R_0402_1005Metric; MPN FRC0402F4871TS; JLCPCB_PN C5203997
R1303, R1305: 100k 1% 1/16W; R_0402_1005Metric; MPN 0402WGF1003TCE; JLCPCB_PN C25741
R1306: 64.9k 1% 1/16W; R_0402_1005Metric; MPN FRC0402F6492TS; JLCPCB_PN C5713275
R1307: 1R 5% 1/16W; R_0402_1005Metric; MPN FRC0402J1R0 TS; JLCPCB_PN C2906901
TP1301: +3V3_D; TestPoint_Pad_D1.0mm; MPN DNP-NO-COMPONENT; LCSC N/A
TP1302: BUCK_SYNC; TestPoint_Pad_D1.0mm; MPN PCB pad (no part)
TP1303: +3V3_A; TestPoint_Pad_D1.0mm; MPN DNP-NO-COMPONENT; LCSC N/A
U1301: TPS62913RPUR; Texas_RPU0010A_VQFN-HR-10_2x2mm_P0.5mm; MPN TPS62913RPUR; JLCPCB_PN C5189914
U1302: TPS7A4701RGWR; Texas_RGW0020A_VQFN-20-1EP_5x5mm_P0.65mm_EP3.15x3.15mm_Ther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; MPN TPS7A4701RGWR; JLCPCB_PN C90084

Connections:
+3V3_A: FL1301.3; also elsewhere on the board
+3V3_D: C1301.1, C1302.1, C1303.1, C1311.1, FB1301.1, L1301.2, R1301.1, TP1301.1 (1_1), U1301.3 (VO), U1302.1 (OUT), U1302.3 (SENSE/FB), U1302.20 (OUT); also elsewhere on the board
/3.3 V supplies/+3V3_A_PRE: C1313.1, C1314.1, FB1301.2, FL1301.1, R1307.1, TP1303.1 (1_1)
/3.3 V supplies/A3V3_DAMP: C1315.1, R1307.2
/3.3 V supplies/BUCK_FB: R1301.2, R1302.2, U1301.9 (FB)
/3.3 V supplies/BUCK_NRSS: C1308.1, U1301.8 (NR/SS)
/3.3 V supplies/BUCK_PG: U1301.5 (PG); also elsewhere on the board
/3.3 V supplies/BUCK_SCONF: R1304.1, U1301.10 (S-CONF)
/3.3 V supplies/BUCK_SW: L1301.1, U1301.2 (SW)
/3.3 V supplies/BUCK_SYNC: C1307.1, R1303.1, TP1302.1 (1_1), U1301.1 (EN/SYNC); also elsewhere on the board
/3.3 V supplies/LDO_EN: R1305.2, R1306.1, U1302.13 (EN); also elsewhere on the board
/3.3 V supplies/LDO_NR: C1312.1, U1302.14 (NR)
GND: C1301.2, C1302.2, C1303.2, C1304.2, C1305.2, C1306.2, C1307.2, C1308.2, C1309.2, C1310.2, C1311.2, C1312.2, C1313.2, C1314.2, C1315.2, FL1301.2, R1302.1, R1303.2, R1304.2, R1306.2, U1301.4 (PGND), U1301.7 (PSNS), U1302.7 (GND), U1302.8 (1.6V), U1302.11 (0.2V), U1302.12 (0.1V), U1302.21 (EP); also elsewhere on the board
VSYS: C1304.1, C1305.1, C1306.1, C1309.1, C1310.1, R1305.1, U1301.6 (VIN), U1302.15 (IN), U1302.16 (IN); also elsewhere on the board

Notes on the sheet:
U1302 runs +3V3_D in RECORD mode. Pins 8, 11, 12 to GND: 1.4 + 1.6 + 0.2 + 0.1 = 3.3 V. EN = LDO_EN: the R1305/R1306 divider from VSYS keeps U1302 on at reset (EN <= IN + 0.4 V). U401 PC13 pulls LDO_EN low to turn U1302 off. U1301 PG drives BUCK_PG to U401 PD3. SCREEN -> RECORD: U1302 on, then U130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
ANALOG RAIL FILTER: +3V3_D -> FB1301 -> FL1301 -> +3V3_A
SCREEN MODE BUCK: U1301 TPS62913
RECORD MODE LDO: U1302 TPS7A4701
U1301 runs +3V3_D in SCREEN mode (ECO-002). EN/SYNC = BUCK_SYNC: clock at 3 x fs = 2.1818 MHz = on and locked; held low >= 10 us = off. R1303 holds it low at reset, so the board starts in RECORD on U1302. R1301/R1302 15.4k / 4.87k: 3.330 V (VFB 0.8 V; R2 <= 5 kOhm, SLVSFP4B 8.2.2.2.6). R1304 4.87k 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
INTERFACES VSYS in: from the Battery, charger and USB-C sheet. +3V3_D out: U1301 in SCREEN, U1302 in RECORD, to the digital sheets. +3V3_A out: through FB1301 and FL1301, to the analog sheets and U401 VDDA. BUCK_SYNC in: U401 PB1 (TIM8_CH3N) through R404 on the MCU sheet. LDO_EN in: U401 PC13. BUCK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
FB1301 filters +3V3_D into +3V3_A_PRE; R1307/C1315 damp the FB1301 resonance (rule R57). FL1301 (NFM18, no ferrite) is the RF filter into +3V3_A: about -59 to -68 dB at 64/128 MHz. Place FL1301 where the +3V3_A trunk crosses the AFE ring east wall. FB1301 filters the positive supply; it is not a gr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
3.3 V supplies
